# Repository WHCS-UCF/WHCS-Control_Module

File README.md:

# WHCS Control Module Design

The EAGLE source files for WHCS' control module.

## Requirements
EAGLE

## Board Front

## Board Back

### Author
Jimmy Campbell<br/>
*Computer Engineer*

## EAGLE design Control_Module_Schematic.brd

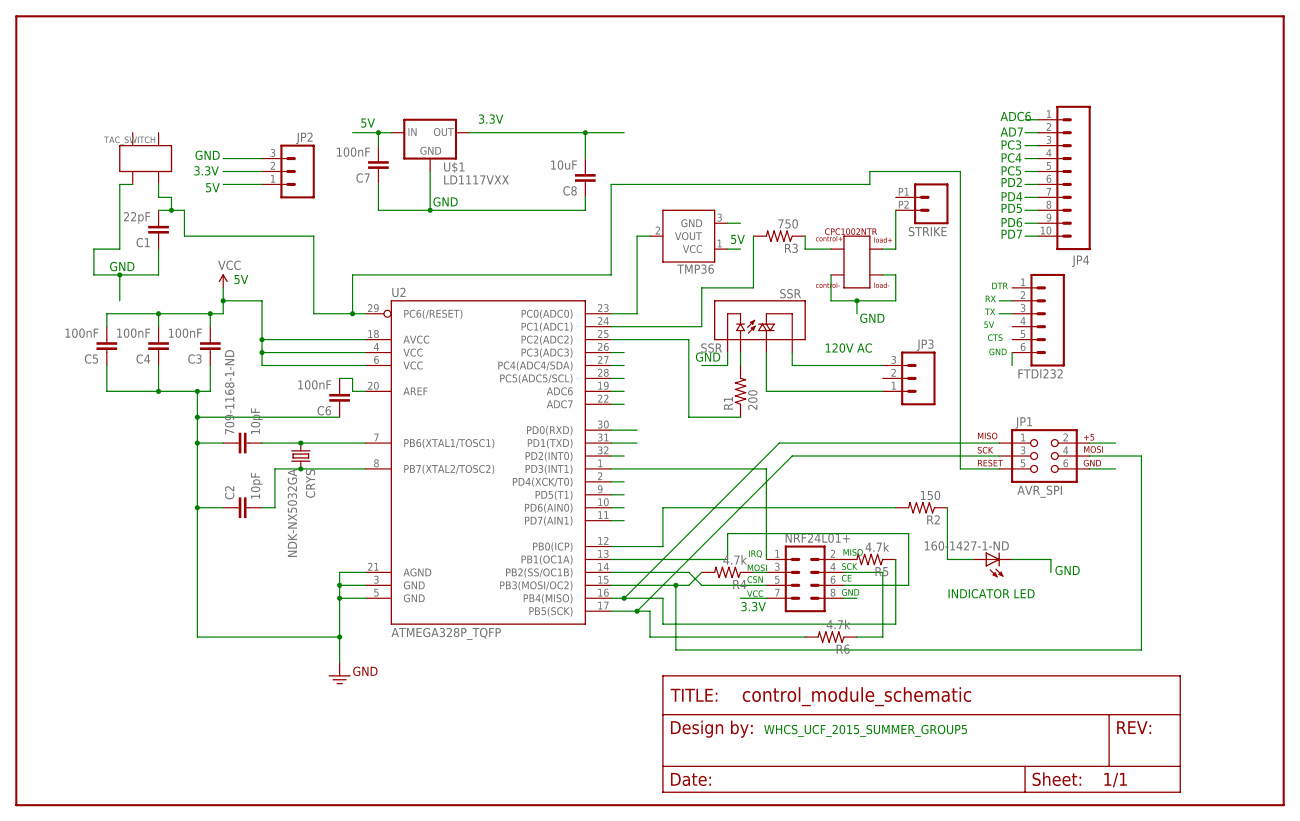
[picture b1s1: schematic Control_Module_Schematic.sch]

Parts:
160-1427-1-ND: LEDCHIP-LED0805; CHIP-LED0805
709-1168-1-ND: 10pF; 0805-CAP
C1: 22pF; 0805-CAP
C2: 10pF; 0805-CAP
C3, C4, C5, C6, C7: 100nF; 0805-CAP
C8: 10uF; 0805-CAP
CPC1002NTR: CPC1002NTR; CPC1002N
CRYS: NDK-NX5032GA; CRYS-5X3.2
FRAME1: FRAME-LETTERNO_PACKAGE; DUMMY
FTDI232: M06LONGPADS; 1X06_LONGPADS
JP1: AVR_SPI; 2X3-NS
JP2, JP3: M03-SCREW-5MM; SCREWTERMINAL-5MM-3
JP4: M10LOCK_LONGPADS; 1X10_LOCK_LONGPADS
NRF24L01+: M04X2; 2X4
R1: 200; R0805
R2: 150; R0805
R3: 750; R0805
R4, R5, R6: 4.7k; R0805
SSR: SSR; RELAY-S116S02F
STRIKE: M022.54MM_SCREWTERM; 1X02_2.54_SCREWTERM
TAC_SWITCH: TACTILE_SWITCH; TAC_SWITCH_GULL_WING
TMP36: TMP36TO-92-KIT; TO-92-KIT
U2: ATMEGA328P_TQFP; TQFP32-08
U$1: LD1117VXX; 78XXL

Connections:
3.3V: C8.2, JP2.2, NRF24L01+.7, U$1.OUT
5V: C3.2, C4.2, C5.2, C7.2, JP1.2, JP2.1, TMP36.1 (VCC), U2.4 (VCC), U2.6 (VCC), U2.18 (AVCC), U$1.IN
ADC6: JP4.1, U2.19 (ADC6)
ADC7: JP4.2, U2.22 (ADC7)
GND: 160-1427-1-ND.C, 709-1168-1-ND.1, C1.1, C2.1, C3.1, C4.1, C5.1, C6.1, C7.1, C8.1, CPC1002NTR.P$1, CPC1002NTR.P$4, FTDI232.6, JP1.6, JP2.3, NRF24L01+.8, SSR.P$4 (-), TAC_SWITCH.P$2, TMP36.3 (GND), U2.3 (GND), U2.5 (GND), U2.21 (AGND), U$1.GND
unnamed: NRF24L01+.5, U2.14 (PB2(SS/OC1B))
unnamed: JP1.1, R5.1, U2.16 (PB4(MISO))
unnamed: JP1.4, R4.2, U2.15 (PB3(MOSI/OC2))
unnamed: JP1.3, R6.2, U2.17 (PB5(SCK))
unnamed: NRF24L01+.1, U2.1 (PD3(INT1))
unnamed: NRF24L01+.6, U2.13 (PB1(OC1A))
unnamed: TMP36.2 (VOUT), U2.23 (PC0(ADC0))
unnamed: R1.2, SSR.P$3 (+)
unnamed: R1.1, U2.25 (PC2(ADC2))
unnamed: JP3.3, SSR.P$1 (T1)
unnamed: JP3.1, SSR.P$2 (T2)
unnamed: R3.2, U2.24 (PC1(ADC1))
unnamed: CPC1002NTR.P$2 (CONTROL+), R3.1
unnamed: 709-1168-1-ND.2, CRYS.P$1 (1), U2.7 (PB6(XTAL1/TOSC1))
unnamed: C2.2, CRYS.P$2 (2), U2.8 (PB7(XTAL2/TOSC2))
unnamed: R2.2, U2.12 (PB0(ICP))
unnamed: 160-1427-1-ND.A, R2.1
unnamed: CPC1002NTR.P$3, STRIKE.P2 (2)
unnamed: NRF24L01+.3, R4.1
unnamed: NRF24L01+.2, R5.2
unnamed: NRF24L01+.4, R6.1
unnamed: C6.2, U2.20 (AREF)
unnamed: C1.2, JP1.5, TAC_SWITCH.P$4, U2.29 (PC6(/RESET))
PC3: JP4.3, U2.26 (PC3(ADC3))
PC4: JP4.4, U2.27 (PC4(ADC4/SDA))
PC5: JP4.5, U2.28 (PC5(ADC5/SCL))
PD2: JP4.6, U2.32 (PD2(INT0))
PD4: JP4.7, U2.2 (PD4(XCK/T0))
PD5: JP4.8, U2.9 (PD5(T1))
PD6: JP4.9, U2.10 (PD6(AIN0))
PD7: JP4.10, U2.11 (PD7(AIN1))
RXD: FTDI232.3, U2.30 (PD0(RXD))
TXD: FTDI232.2, U2.31 (PD1(TXD))

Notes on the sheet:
IRQ
MOSI
CSN
VCC
MISO
SCK
GND
120V AC
3.3V
INDICATOR LED
DTR
CTS
ADC6
AD7
PC3
PC4
PC5
PD2
PD4
PD5
PD6
PD7
WHCS_UCF_2015_SUMMER_GROUP5

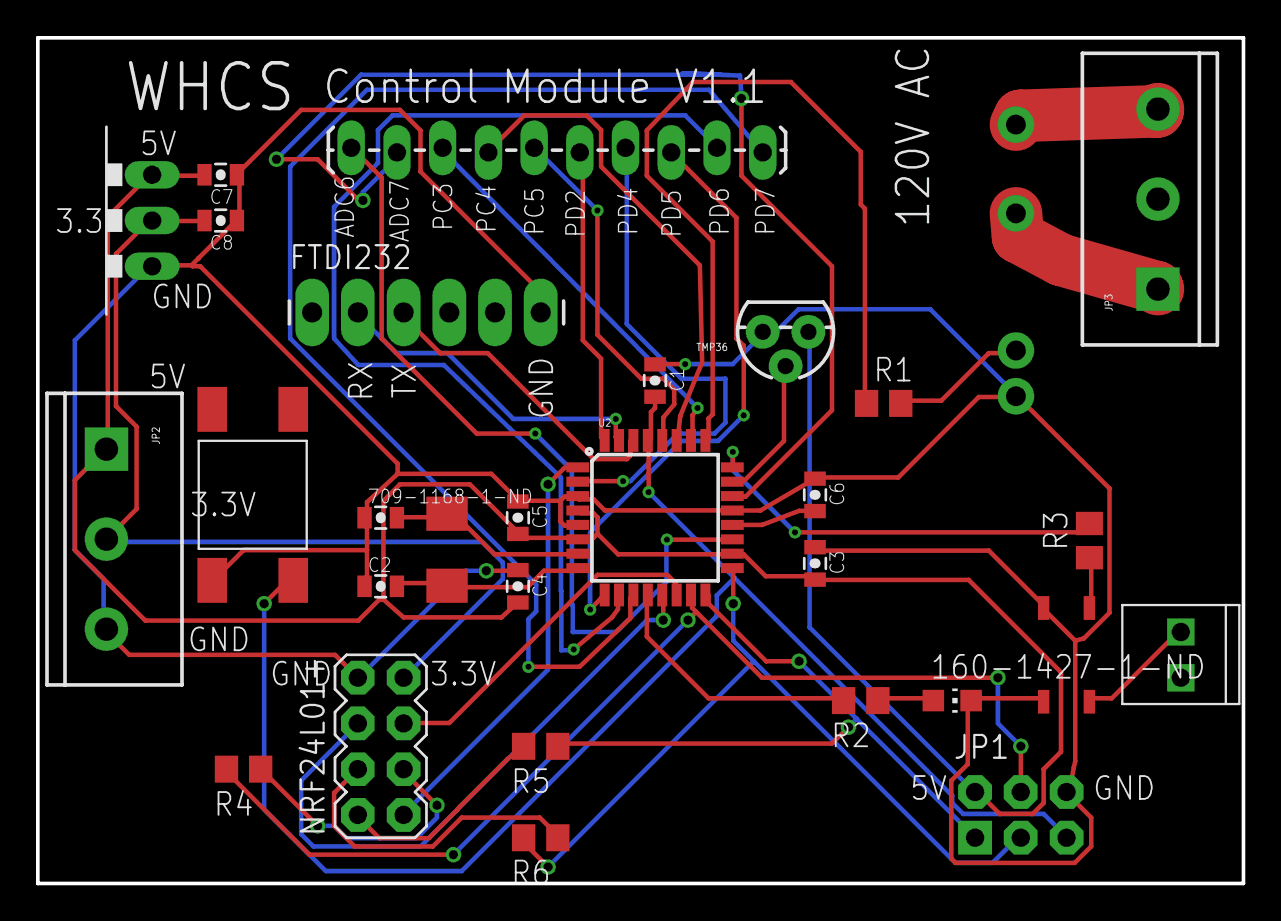
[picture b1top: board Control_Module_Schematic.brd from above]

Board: 2 copper layers, 67.0 x 47.0 mm, 31 parts (0 on the bottom side), 38 nets.

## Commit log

2015-05-22 Made the layout for the board.
2015-05-26 Board status when first submitted.
    This is the way the board was when first submitted to Oshpark for an
    initial run.
2015-05-29 fixed drc fail. Two vias were too close together at the top right of the mcu
2015-05-29 Cleaning up unnecessary files.
2015-05-29 update gitignore.
2015-06-10 Changed the pin that controls the door strike
2015-06-10 Enhanced crystal footprint
    Also did some changing of the route placements to make them have better
    spacing.
    Added documentation to the TPlace layer to show how the power should be
    connected.
2015-06-10 Did some route optimization
2015-06-10 Connected the FTDI232 UART chip's GND to GND
2015-06-11 AC solid state relay pin change
    The AC SSR is now controlled by pc2 from the atmega328. The previous pin
    used to control it ADC7 was not capable of producing output and it has
    been rerouted to the breakout header.
2015-06-17 Added tactile switch for reset
    Also did some manual routing optimizations
2015-06-18 Final changes before placing oshpark 2nd order.
2015-07-30 Add boardshots and readme.md

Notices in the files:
parts and their libraries:
SparkFun-Capacitors: Licensing: Creative Commons ShareAlike 4.0 International - https://creativecommons.org/licenses/by-sa/4.0
WHCS: Released under the Creative Commons Attribution Share-Alike 4.0 License
WHCS: https://creativecommons.org/licenses/by-sa/4.0
